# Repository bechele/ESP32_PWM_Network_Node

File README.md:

## Network device to drive Servos for Animatronics:

With the latest Software 3.0 the Bechele software (https://github.com/bechele/bechele) now supports beside the existing PCA9685 PWM Boards also network devices, based on cheap ESP32 modules. Each network device may handle 16 Servos or 16 Relais or a desired mixture of both. All the data transfers from the Host (Raspi) is realized using broadcast transmissions, where all devices (nodes) receive the same data packets. According to the node configuration, the node takes the data from the packet that is intended for it. This way there is plenty of time to drive 700 Servos @ 44 ESP32 nodes, or 11000 relais @ 700 nodes with a 50ms refresh rate. Network devices may be connected via Ethernet or WiFi. Of course Ethernet driven nodes are more stable than via Wifi. The board exists in two flavours. A smaller SMD version and a larger version unsing conventional parts. For both versions you may download the gerber files and also the kicad source, so you can order a PCB from your desired PCB manufacturer. The smd version is for skilled people who know how to handle and solder SMD parts. The conventional Version uses mainly larger parts that are much easier to solder onto the PCB. Which one you use is up to you. The function is identical.<br><br>
**Note: Using Wifi is by far not as safe as using ethernet. To use WiFi, you need to make sure, the WiFi router is very close to the network devices, since the RSSI (Received Signal Strength Indicator) must be below 70 dB, (you may read the RSSI value during boot, when connecting a serial monitor to the TX pin of the device). Otherwise you will notice lots of missing packets – means the movement of your servos will be not continuous. Also you need an environment where there are only few other Wifi radio sources. If there is a lot of other traffic around, you will encounter the same problems. This is due to the working principle of WiFi and has nothing to do with the software. Wifi is not intended for real time control of devices ! So my recommendation is to use W5500 Ethernet modules. In a test using Ethernet with 700 configured Servos @ 50 ms refresh rate (means every 50 ms all servos got new data), none of the packets went lost over a longer time, so ethernet is quite safe.**

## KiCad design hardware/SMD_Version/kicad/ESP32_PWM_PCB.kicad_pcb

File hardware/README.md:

## The ESP32_PWM_NODE_PCB exists in two flavours:
- A SMD based version for skilled people, able to solder tiny SMD parts, or for automatic assembled PCBs.
- A PCB based on conventional parts for easier assembly.

Note: Both PCBs have an identical function and run with the same firmware.

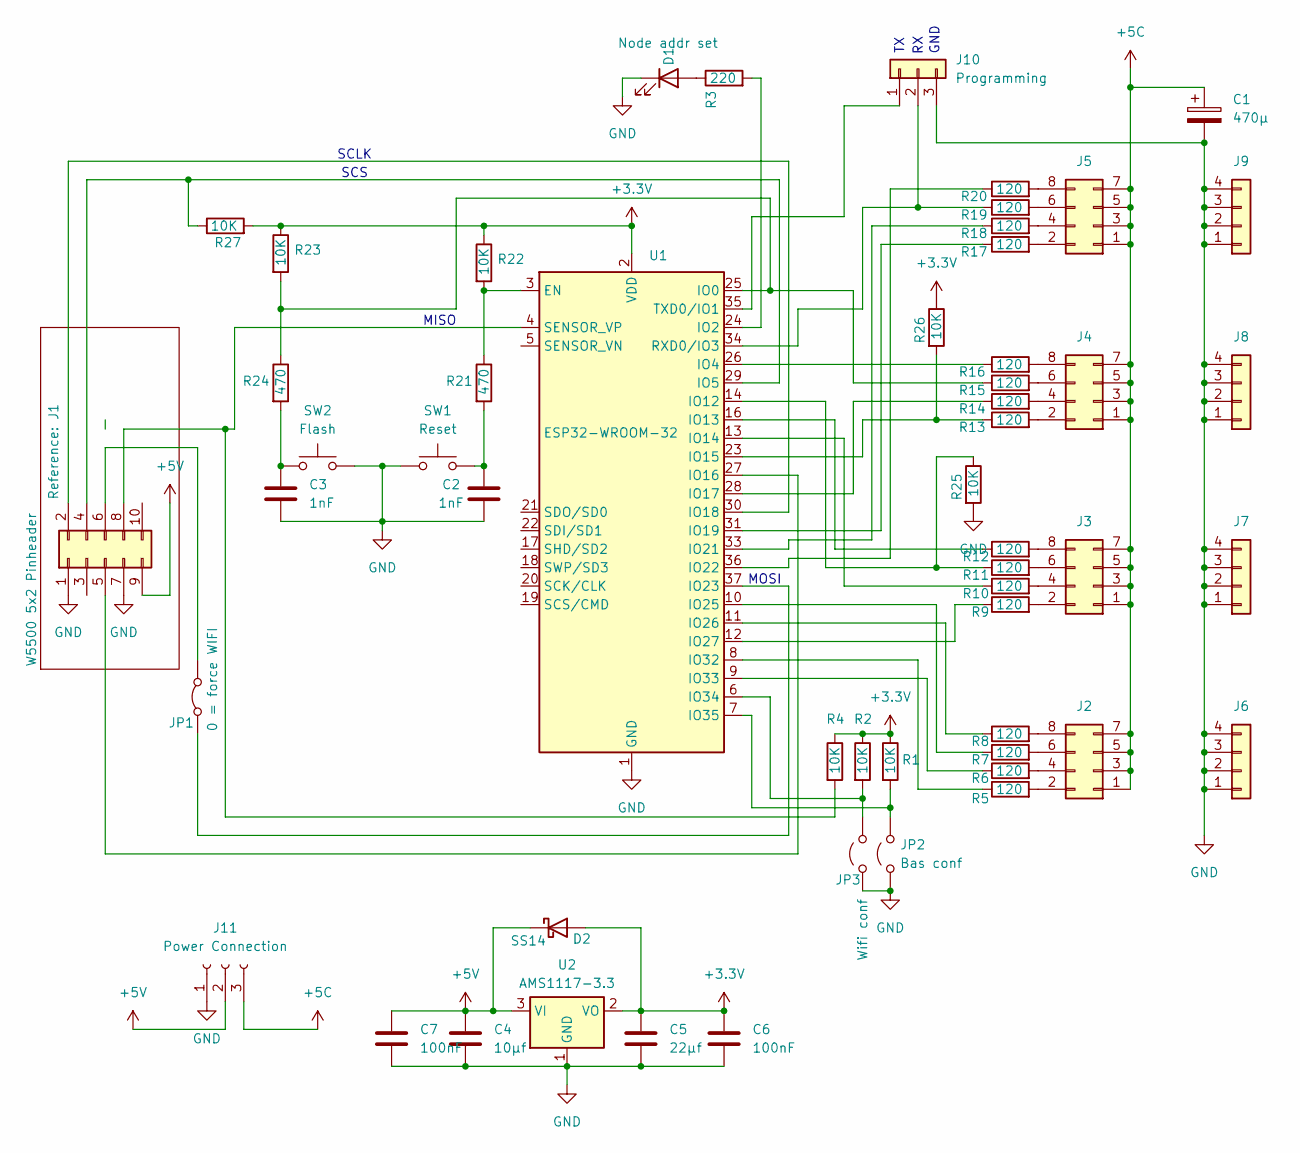
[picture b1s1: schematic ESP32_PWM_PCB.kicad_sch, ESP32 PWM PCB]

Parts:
C1: 470µ; CP_Radial_D8.0mm_P3.50mm
C2, C3: 1nF; C_0603_1608Metric
C4: 10µf; C_1206_3216Metric
C5: 22µf; C_1206_3216Metric
C6, C7: 100nF; C_0603_1608Metric
D1: Node addr set; LED_D3.0mm
D2: SS14; D_SMA
J1: W5500 5x2 Pinheader; W5500_Modul
J2, J3, J4, J5: PinHeader_2x04_P2.54mm_Vertical
J6, J7, J8, J9: PinHeader_1x04_P2.54mm_Vertical
J10: Programming; PinHeader_1x03_P2.54mm_Vertical
J11: Power Connection; TE_826576-3_1x03_P3.96mm_Vertical
JP1: 0 = force WIFI; PinHeader_1x02_P2.54mm_Vertical
JP2: Bas conf; PinHeader_1x02_P2.54mm_Vertical
JP3: Wifi conf; PinHeader_1x02_P2.54mm_Vertical
R1, R2, R4, R22, R23, R25, R26, R27: 10K; R_0603_1608Metric
R3: 220; R_0603_1608Metric
R5, R6, R7, R8, R9, R10, R11, R12, R13, R14, R15, R16, R17, R18, R19, R20: 120; R_0603_1608Metric
R21, R24: 470; R_0603_1608Metric
SW1: Reset; SW_SPST_SKQG_WithoutStem
SW2: Flash; SW_SPST_SKQG_WithoutStem
U1: ESP32-WROOM-32
U2: AMS1117-3.3; SOT-223-3_TabPin2

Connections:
+3.3V: C5.1, C6.1, D2.2 (A), R1.1, R2.1, R4.1, R22.1, R23.1, R26.1, R27.2, U1.2 (VDD), U2.2 (VO)
+5C: C1.1, J2.1, J2.3, J2.5, J2.7, J3.1, J3.3, J3.5, J3.7, J4.1, J4.3, J4.5, J4.7, J5.1, J5.3, J5.5, J5.7, J11.3
+5V: C4.1, C7.1, D2.1 (K), J1.9 (5V), J11.2, U2.3 (VI)
GND: C1.2, C2.2, C3.2, C4.2, C5.2, C6.2, C7.2, D1.1 (K), J1.1 (GND), J1.7 (GND), J6.1, J6.2, J6.3, J6.4, J7.1, J7.2, J7.3, J7.4, J8.1, J8.2, J8.3, J8.4, J9.1, J9.2, J9.3, J9.4, J10.3, J11.1, JP2.1 (A), JP3.1 (A), R25.2, SW1.1, SW2.2, U1.1 (GND), U1.15 (GND), U1.38 (GND), U1.39 (GND), U2.1 (GND)
unnamed: C2.1, R21.2, SW1.2
unnamed: C3.1, R24.2, SW2.1
unnamed: D1.2 (A), R3.1
unnamed: J1.8 (MISO), R4.2, U1.4 (SENSOR_VP)
unnamed: J1.6 (MOSI), JP1.2 (B)
unnamed: J1.5 (RST), U1.27 (IO16)
unnamed: J1.2 (SCLK), U1.30 (IO18)
unnamed: J1.4 (SCS), R27.1, U1.29 (IO5)
unnamed: J2.2, R5.2
unnamed: J2.4, R6.2
unnamed: J2.6, R7.2
unnamed: J2.8, R8.2
unnamed: J3.2, R9.2
unnamed: J3.4, R10.2
unnamed: J3.6, R11.2
unnamed: J3.8, R12.2
unnamed: J4.2, R13.2
unnamed: J4.4, R14.2
unnamed: J4.6, R15.2
unnamed: J4.8, R16.2
unnamed: J5.2, R17.2
unnamed: J5.4, R18.2
unnamed: J5.6, R19.2
unnamed: J5.8, R20.2
unnamed: J10.1, U1.35 (TXD0/IO1)
unnamed: J10.2, R19.1, U1.34 (RXD0/IO3)
unnamed: JP1.1 (A), U1.37 (IO23)
unnamed: JP2.2 (B), R1.2, U1.7 (IO35)
unnamed: JP3.2 (B), R2.2, U1.6 (IO34)
unnamed: R21.1, R22.2, U1.3 (EN)
unnamed: R15.1, R23.2, R24.1, U1.25 (IO0)
unnamed: R3.2, U1.24 (IO2)
unnamed: R16.1, U1.26 (IO4)
unnamed: R11.1, R25.1, U1.14 (IO12)
unnamed: R12.1, U1.16 (IO13)
unnamed: R10.1, U1.13 (IO14)
unnamed: R13.1, R26.2, U1.23 (IO15)
unnamed: R14.1, U1.28 (IO17)
unnamed: R17.1, U1.31 (IO19)
unnamed: R18.1, U1.33 (IO21)
unnamed: R20.1, U1.36 (IO22)
unnamed: R7.1, U1.10 (IO25)
unnamed: R8.1, U1.11 (IO26)
unnamed: R9.1, U1.12 (IO27)
unnamed: R5.1, U1.8 (IO32)
unnamed: R6.1, U1.9 (IO33)

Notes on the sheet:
GND
MOSI
SCLK
SCS
MISO

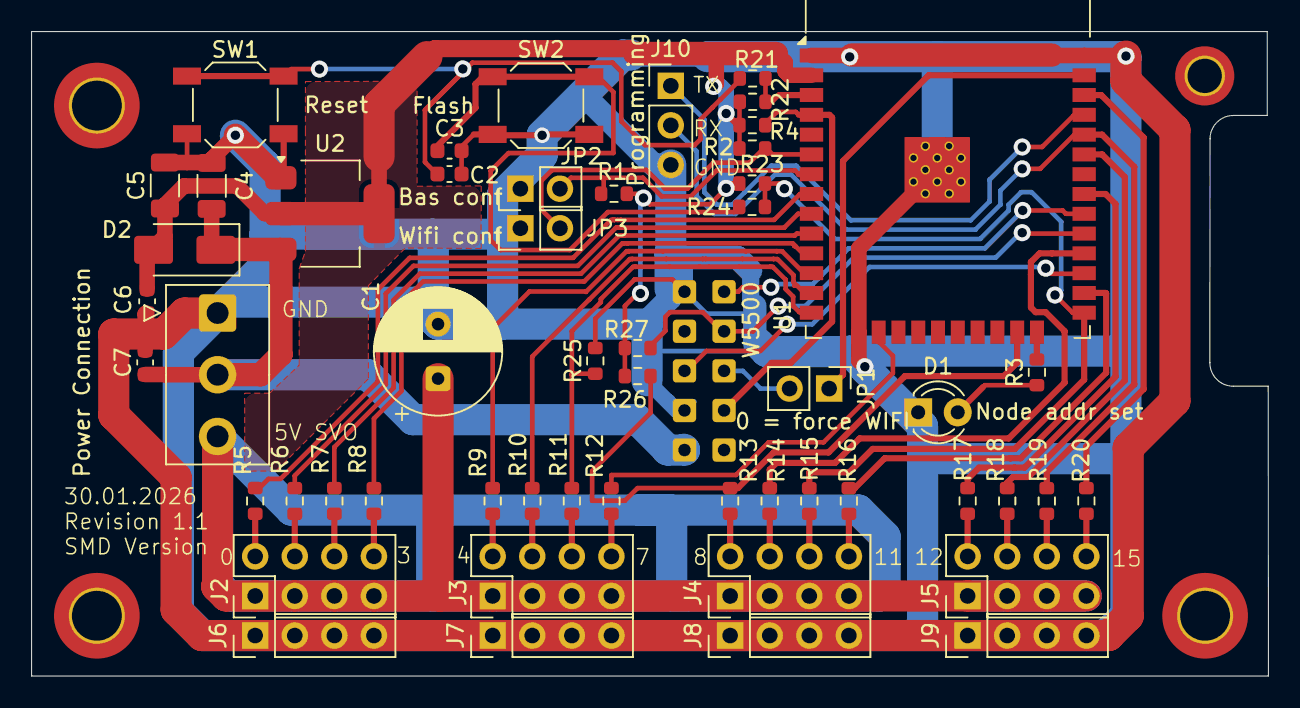
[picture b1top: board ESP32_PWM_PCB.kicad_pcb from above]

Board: 2 copper layers, 79.4 x 41.4 mm, 54 parts (0 on the bottom side), 50 nets.

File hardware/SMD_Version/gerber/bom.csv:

Designator,Footprint,Quantity,Value,LCSC Part #
C1,CP_Radial_D8.0mm_P3.50mm,1,470µ,
"C2, C3",0603,2,1nF,
C4,1206,1,10µf,
C5,1206,1,22µf,
"C6, C7",0603,2,100nF,
D1,LED_D3.0mm,1,Node addr set,
D2,D_SMA,1,SS14,
J1,W5500_Modul,1,W5500,
J10,PinHeader_1x03_P2.54mm_Vertical,1,Programming,
J11,TE_826576-3_1x03_P3.96mm_Vertical,1,Power Connection,
"J2, J3, J4, J5",PinHeader_2x04_P2.54mm_Vertical,4,~,
"J6, J7, J8, J9",PinHeader_1x04_P2.54mm_Vertical,4,~,
JP1,PinHeader_1x02_P2.54mm_Vertical,1,0 = force WIFI,
JP2,PinHeader_1x02_P2.54mm_Vertical,1,Bas conf,
JP3,PinHeader_1x02_P2.54mm_Vertical,1,Wifi conf,
"R1, R2, R22, R23, R25, R26, R27, R4",0603,8,10K,
"R10, R11, R12, R13, R14, R15, R16, R17, R18, R19, R20, R5, R6, R7, R8, R9",0603,16,120,
"R21, R24",0603,2,470,
R3,0603,1,220,
SW1,SW_SPST_SKQG_WithoutStem,1,Reset,
SW2,SW_SPST_SKQG_WithoutStem,1,Flash,
U1,ESP32-WROOM-32,1,ESP32-WROOM-32,
U2,SOT-223-3_TabPin2,1,AMS1117-3.3,

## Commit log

2026-02-08 Update esp32_pwm1.2.ino - adding license
2026-02-08 Add image of a node
2026-02-08 Update README.md - adding an image
2026-02-09 Add a data flowhart
    This data flowchart shows the datagram structure of a broadcast packets sent to the network
